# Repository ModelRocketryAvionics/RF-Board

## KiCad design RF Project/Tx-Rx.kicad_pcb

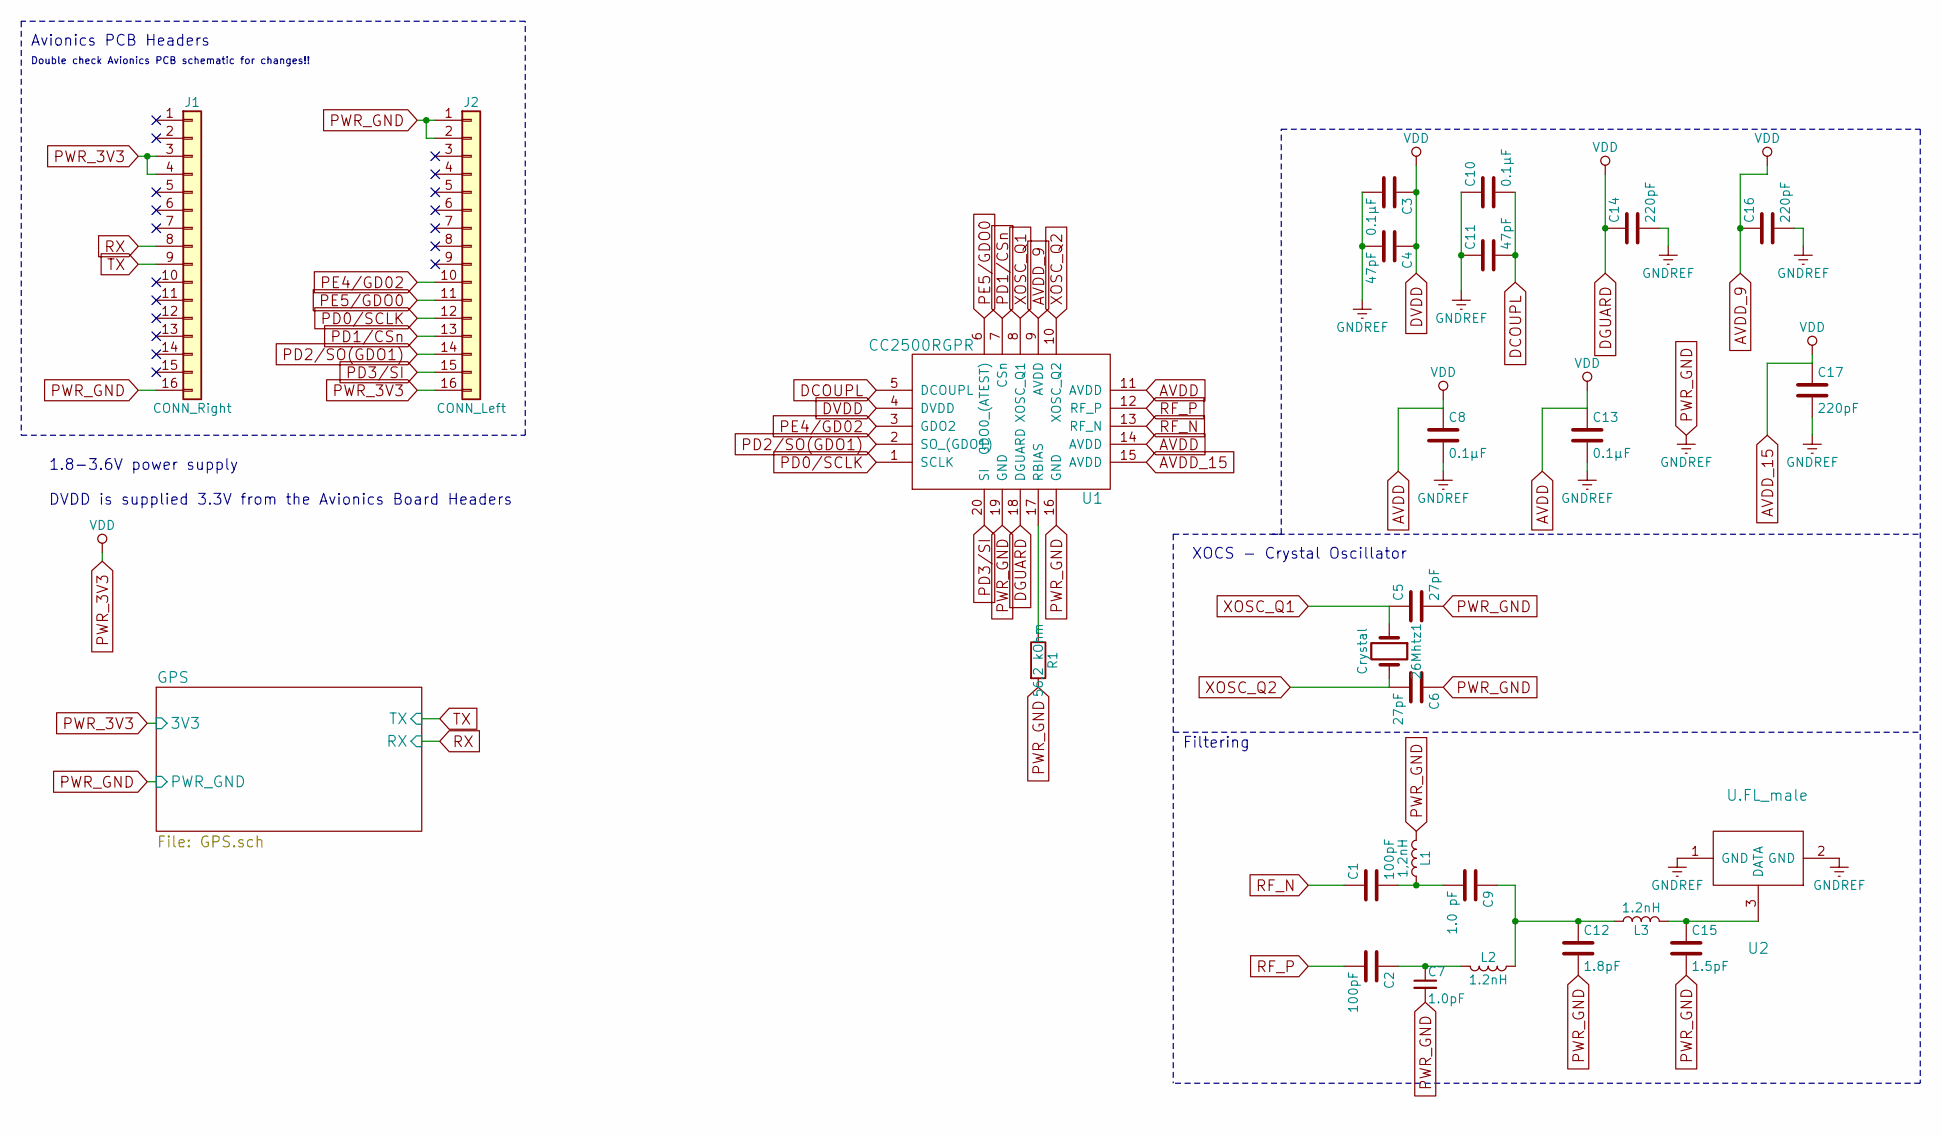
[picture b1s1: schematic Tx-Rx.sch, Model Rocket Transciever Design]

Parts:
26Mhtz1: Crystal; CC2500
C1: 100pF; VENUS634FLPX
C2: 100pF; C_0402
C3, C8, C10, C13: 0.1μF; C_0402
C4, C11: 47pF; C_0402
C5, C6: 27pF; C_0402
C7: 1.0pF; C_0402
C9: 1.0 pF; C_0402
C12: 1.8pF; C_0402
C14, C16, C17: 220pF; C_0402
C15: 1.5pF; C_0402
J1: CONN_Right; Pin_Header_Straight_1x16_Pitch2.54mm
J2: CONN_Left; Pin_Header_Straight_1x16_Pitch2.54mm
L1: 1,2nH; L_0402
L2, L3: 1.2nH; L_0402
R1: 56.2 kOhm; R_0402; Digikey Part No. CR0402-FX-5622GLFCT-ND
U1: CC2500RGPR; CC2500
U2: U.FL_male; u.fl_male

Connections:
DCOUPL: C10.2, C11.2, U1.5 (DCOUPL)
unnamed: C1.2, C9.2, L1.1
unnamed: C2.1, C7.1, L2.2
unnamed: C9.1, C12.1, L2.1, L3.1
unnamed: C15.1, L3.2, U2.3 (DATA)
unnamed: R1.1, U1.17 (RBIAS)
PD0/SCLK: J2.12, U1.1 (SCLK)
PD1/CSn: J2.13, U1.7 (CSn)
PD2/SO(GDO1): J2.14, U1.2 (SO_(GDO1))
PD3/SI: J2.15, U1.20 (SI)
PE4/GD02: J2.10, U1.3 (GDO2)
PE5/GDO0: J2.11, U1.6 (GDO0_(ATEST))
PWR_GND: C3.2, C4.2, C5.2, C6.1, C7.2, C8.2, C10.1, C11.1, C12.2, C13.2, C14.2, C15.2, C16.2, C17.2, J1.16, J2.1, J2.2, L1.2, R1.2, U1.16 (GND), U1.19 (GND), U2.1 (GND), U2.2 (GND); also elsewhere on the board
RF_N: C1.1, U1.13 (RF_N)
RF_P: C2.2, U1.12 (RF_P)
RX: J1.8; also elsewhere on the board
TX: J1.9; also elsewhere on the board
XOSC_Q1: 26Mhtz1.1, C5.1, U1.8 (XOSC_Q1)
XOSC_Q2: 26Mhtz1.2, C6.2, U1.10 (XOSC_Q2)

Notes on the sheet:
1.8-3.6V power supply DVDD is supplied 3.3V from the Avionics Board Headers
XOCS - Crystal Oscillator
Filtering
Avionics PCB Headers
Double check Avionics PCB schematic for changes!!

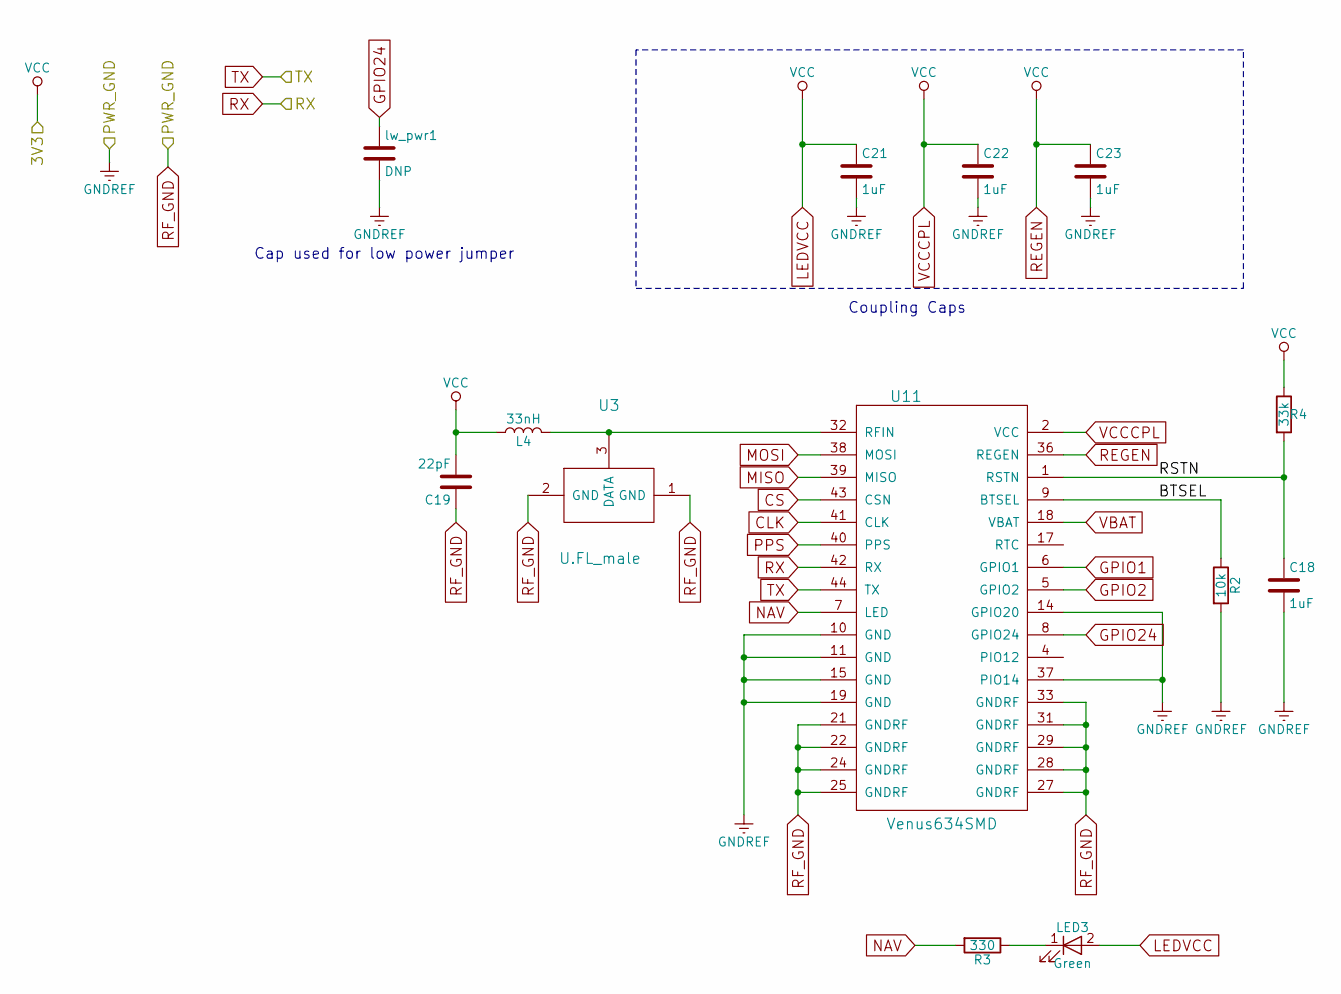
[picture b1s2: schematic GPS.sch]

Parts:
C18, C21, C22, C23: 1uF; C_0402
C19: 22pF; C_0402
L4: 33nH; L_0402
LED3: Green; LED_0402
R2: 10k; R_0402
R3: 330; R_0402
R4: 33k; R_0402
U3: U.FL_male; u.fl_male
U11: Venus634SMD; VENUS634FLPX
lw_pwr1: DNP; C_0402

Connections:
/GPS/BTSEL: R2.1, U11.9 (BTSEL)
/GPS/RSTN: C18.1, R4.2, U11.1 (RSTN)
CLK: U11.41 (CLK)
CS: U11.43 (CSN)
GPIO1: U11.6 (GPIO1)
GPIO2: U11.5 (GPIO2)
GPIO24: U11.8 (GPIO24), lw_pwr1.1
MISO: U11.39 (MISO)
MOSI: U11.38 (MOSI)
unnamed: LED3.1 (K), R3.1
PPS: U11.40 (PPS)
PWR_GND: C18.2, C19.1, C21.2, C22.2, C23.2, R2.2, U3.1 (GND), U3.2 (GND), U11.10 (GND), U11.11 (GND), U11.14 (GPIO20), U11.15 (GND), U11.19 (GND), U11.21 (GNDRF), U11.22 (GNDRF), U11.24 (GNDRF), U11.25 (GNDRF), U11.27 (GNDRF), U11.28 (GNDRF), U11.29 (GNDRF), U11.31 (GNDRF), U11.33 (GNDRF), U11.37 (PIO14), lw_pwr1.2; also elsewhere on the board
RX: U11.42 (RX); also elsewhere on the board
TX: U11.44 (TX); also elsewhere on the board
VBAT: U11.18 (VBAT)

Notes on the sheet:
Cap used for low power jumper
Coupling Caps

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
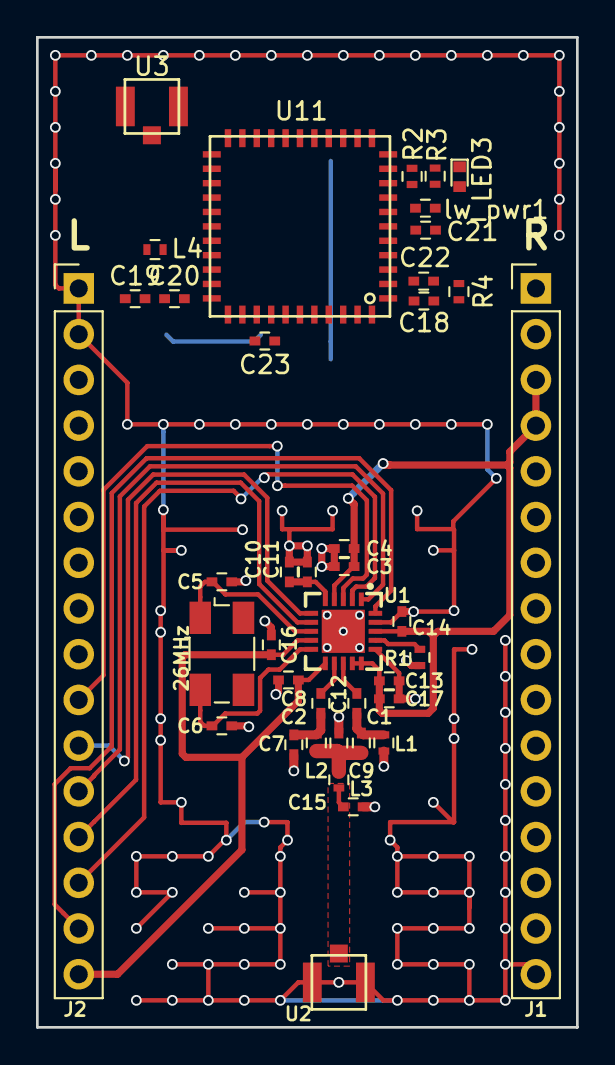
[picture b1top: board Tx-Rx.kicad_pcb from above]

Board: 2 copper layers, 30.0 x 55.0 mm, 40 parts (0 on the bottom side), 24 nets.

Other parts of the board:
C20: 1uF; C_0402

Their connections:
PWR_GND: C20.2; also elsewhere on the board

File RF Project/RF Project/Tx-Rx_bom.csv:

"Id";"Designator";"Package";"Quantity";"Designation";"Supplier and ref";
1;"J2";"Pin_Header_Straight_1x16_Pitch2.54mm";1;"CONN_Left";;;
2;"26MHz";"Crystal_SMD_Abracon_ABM3B-4pin_5.0x3.2mm";1;"Crystal";;;
3;"C1,C2";"C_0402";2;"100pF";;;
4;"C3,C8,C10,C13";"C_0402";4;"0.1μF";;;
5;"C4,C11";"C_0402";2;"47pF";;;
6;"C5,C6";"C_0402";2;"27pF";;;
7;"C7";"C_0402";1;"1.0pF";;;
8;"C9";"C_0402";1;"1.0 pF";;;
9;"C12";"C_0402";1;"1.8pF";;;
10;"C14,C16,C17";"C_0402";3;"220μF";;;
11;"C15";"C_0402";1;"1.5pF";;;
12;"L1";"L_0402";1;"1,2nH";;;
13;"L2,L3";"L_0402";2;"1.2nH";;;
14;"R1";"R_0201";1;"50 kOhm";;;
15;"U1";"CC2500";1;"CC2500RGPR";;;
16;"U2";"u.fl_male";1;"U.FL_male";;;
17;"J1";"Pin_Header_Straight_1x16_Pitch2.54mm";1;"CONN_Right";;;

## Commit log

2018-07-17 Added Avionics Headers to schematic, fixed library link issues (hopefully) and started working on Layout
2018-07-17 Fixed CC2500 footprint (missing gnd pad) finished layout, needs CDR
2018-07-17 fixed Crystal SilkScreen label
2018-07-17 Resurrected kicad_pcb from the grave
2018-07-17 Moved components so that they weren't inside the CC2500 (woops), also changed the resistor to 0402 instead of 0201 since those aren't in stock QQ
2018-07-17 Fixed my poor attempt to move stuff :(
2018-07-17 Labelled headers Left/Right since someone who isn't me totally messed up and put the right header on the left and the left header on the right then did the entire layout and doesn't want to redo it (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
2018-07-17 shifted the headers down by 3.77mm since Harrisons board is centered at 102.5mm not 100mm and I thought 15/2 was 8 (woops). Still haven't swapped left with right, that would take too long :P
2018-07-17 hello
2018-07-17 Fixed stuff and hopefully non gitbash people will actually be able to download and see this..
2018-07-17 Made things more pretty
2018-07-17 fixing..
2018-07-17 finished fixing T's stuff
2018-07-17 finished fixing T's stuff2
2018-07-18 Attempted to increase trace width to reduce impedance mismatch (could only achieve ~1mm or 88.3 Ohm vs the desired 50 Ohm), cleaned up some via placements/fills/silkscreen things
2018-07-18 Exported GRBL files and final .zip
2018-07-20 Fixed disconnection of a via on L1 of the RF output with the GND plane
2018-07-21 Layout Revision 1b complete, notable additions: 1) Moved headers onto correct side, added pads for a RF Shield, main feed line to UFL connector is impedance matched to ~50ohm, incrememted the revisio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
2018-07-21 Added gerbers to Output/
2018-09-10 GPS schematic and pcb track routing
2018-09-10 edit vias
2018-09-20 revision component placement, coupling caps added

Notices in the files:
RF Project/Tx-Rx.sch:
creativecommons.org/liscences/by/4.0
Liscence CC BY 4.0
